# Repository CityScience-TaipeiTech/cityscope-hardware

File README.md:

# CityScope-hardware

## Environment Setup
config path
| Name|Path|
---|---
|CITYSCOPE_LIB|`YOUR_FOLDER_PATH`/cityscope-hardware/libraries
### Config Symbol Library
Preferences -> Manage Symbol Libraries

| Nickname|Library Path|
---|---
|CityScope_Component|${CITYSCOPE_LIB}/CityScope_Component.kicad_sym|

### Config Footprint Library
Preferences -> Manage Footprint Libraries
| Nickname|Library Path|
---|---
|CityScope_Component|${CITYSCOPE_LIB}/CityScope_Component.pretty|
## Generate GERBER Files for Fabrication
### Gerber Plot
In ***File*** -> ***Plot...***

### Drill Plot
In ***File*** -> ***Plot...***

## Generate .pos Files for SMT
- Make sure you set origin point for you .pos file. In the fish head PCB, set FID2 fiducial as origin. Click the icon bellow in tool set to place your origin.

- Files -> Fabrication Outputs -> Component Placement (.pos)

- The following files will be generated.

    1. PROJECT-bottom-pos.csv
    2. PROJECT-top-pos.csv

- Convert the generated file to smt machine format by a python file in `tools/` folder. 
    ``` bash
    python3 convert_form.py --file-name ../YOUR_FOLDER_PATH/PROJECT-top-pos.csv
    ```
- An output.csv will be generated in `tools/`. 
- If the footprint name is too long, for example "JST_SH_BM03B-SRSS-TB_1x03-1MP_P1.00mm_Vertical
", please make it shorter or just delete this row.

## Generating BOM Sheet
### Requirements
- Install BOM extension:`Interactive Html Bom` in the Plugin And Content Manager.

### Generate BOM
- Open your `PCB Editor` -> ***Tools*** -> ***External Plugins*** -> ***Generate Interactive Html Bom***

## Release Files Structure
1. GERBERs/
2. bom/
3. PROJECT_v1_0.pdf
4. PROJECT_3d_v1_0.png
5. PROJECT_3d_v1_0.step
6. PROJECT_gerber_v1_0.zip

# Recommend Plugins
1. Interactive Html Bom
2. pcb-action-tools
3. KiKit
4. KiBuzzard

## KiKit Panelize
### Fisheye configuration
``` json
{
    "layout": {
        "hspace": "3.2mm",
        "vspace": "3.2mm",
        "rotation": "45deg",
        "rows": "6",
        "cols": "5"
    },
    "tabs": {
        "vwidth": "3.2mm",
        "hwidth": "3.2mm"
    },
    "cuts": {
        "type": "mousebites"
    },
    "framing": {
        "type": "frame",
        "hspace": "3.2mm",
        "vspace": "3.2mm",
        "width": "3.2mm"
    }
}
```

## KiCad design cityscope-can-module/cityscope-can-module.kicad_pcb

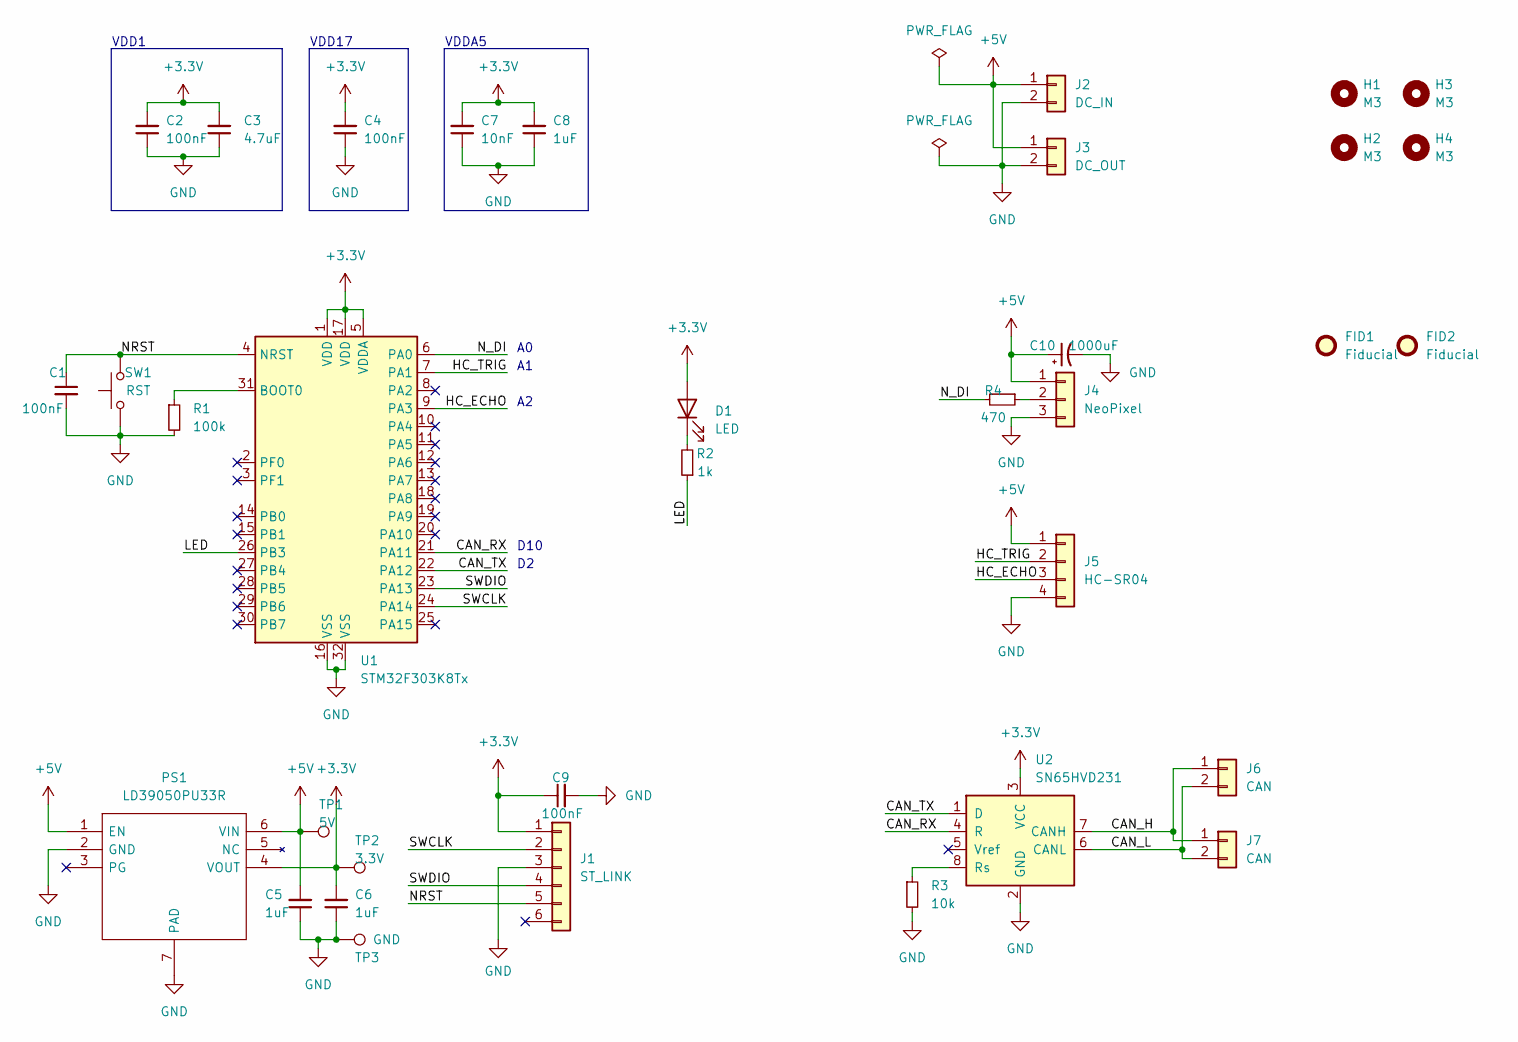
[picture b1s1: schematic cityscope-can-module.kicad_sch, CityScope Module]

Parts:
C1, C2, C4: 100nF; C_0603_1608Metric
C3: 4.7uF; C_0603_1608Metric
C5, C6, C8: 1uF; C_0603_1608Metric
C7: 10nF; C_0603_1608Metric
C9: 100nF; C_0603_1608Metric; Manufacturer_Part_Number CC603KRX7R8BB104; Mouser Part Number 603-CC603KRX7R8BB104
C10: 1000uF; CP_Radial_D8.0mm_P3.50mm
D1: LED; LED_0603_1608Metric
FID1, FID2: Fiducial; Fiducial_0.75mm_Mask1.5mm
H1, H2, H3, H4: M3; MountingHole_3.2mm_M3
J1: ST_LINK; JST_SH_BM06B-SRSS-TB_1x06-1MP_P1.00mm_Vertical; Mouser Part Number local store
J2: DC_IN; AMASS_XT30PW-M_1x02_P2.50mm_Horizontal
J3: DC_OUT; AMASS_XT30PW-F_1x02_P2.50mm_Horizontal
J4: NeoPixel; JST_PH_S3B-PH-SM4-TB_1x03-1MP_P2.00mm_Horizontal
J5: HC-SR04; JST_PH_S4B-PH-SM4-TB_1x04-1MP_P2.00mm_Horizontal
J6, J7: CAN; JST_PH_S2B-PH-SM4-TB_1x02-1MP_P2.00mm_Horizontal
PS1: LD39050PU33R; SON95P300X300X100-7N-D; Manufacturer_Part_Number LD39050PU33R; Mouser Part Number 511-LD39050PU33R
R1: 100k; R_0603_1608Metric
R2: 1k; R_0603_1608Metric
R3: 10k; R_0603_1608Metric
R4: 470; R_0603_1608Metric
SW1: RST; SW_SPST_TL3305A
TP1: 5V; TestPoint_Pad_D1.0mm
TP2: 3.3V; TestPoint_Pad_D1.0mm
TP3: GND; TestPoint_Pad_D1.0mm
U1: STM32F303K8Tx; LQFP-32_7x7mm_P0.8mm
U2: SN65HVD231; SOIC-8_3.9x4.9mm_P1.27mm

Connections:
+3.3V: C2.2, C3.2, C4.2, C6.2, C7.2, C8.2, C9.1, D1.2 (A), J1.1, PS1.4 (VOUT), TP2.1, U1.1 (VDD), U1.5 (VDDA), U1.17 (VDD), U2.3 (VCC)
+5V: C5.2, C10.1, J2.1, J3.1, J4.1, J5.1, PS1.1 (EN), PS1.6 (VIN), TP1.1
/CAN_H: J6.1, J7.1, U2.7 (CANH)
/CAN_L: J6.2, J7.2, U2.6 (CANL)
/CAN_RX: U1.21 (PA11), U2.4 (R)
/CAN_TX: U1.22 (PA12), U2.1 (D)
/HC_ECHO: J5.3, U1.9 (PA3)
/HC_TRIG: J5.2, U1.7 (PA1)
/LED: R2.1, U1.26 (PB3)
/NRST: C1.1, J1.5, SW1.2, U1.4 (NRST)
/N_DI: R4.2, U1.6 (PA0)
/SWCLK: J1.2, U1.24 (PA14)
/SWDIO: J1.4, U1.23 (PA13)
GND: C1.2, C2.1, C3.1, C4.1, C5.1, C6.1, C7.1, C8.1, C9.2, C10.2, J1.3, J2.2, J3.2, J4.3, J5.4, PS1.2 (GND), PS1.7 (PAD), R1.2, R3.2, SW1.1, TP3.1, U1.16 (VSS), U1.32 (VSS), U2.2 (GND)
unnamed: D1.1 (K), R2.2
unnamed: J4.2, R4.1
unnamed: R1.1, U1.31 (BOOT0)
unnamed: R3.1, U2.8 (Rs)

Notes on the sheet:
VDD1
D10
VDDA5
VDD17

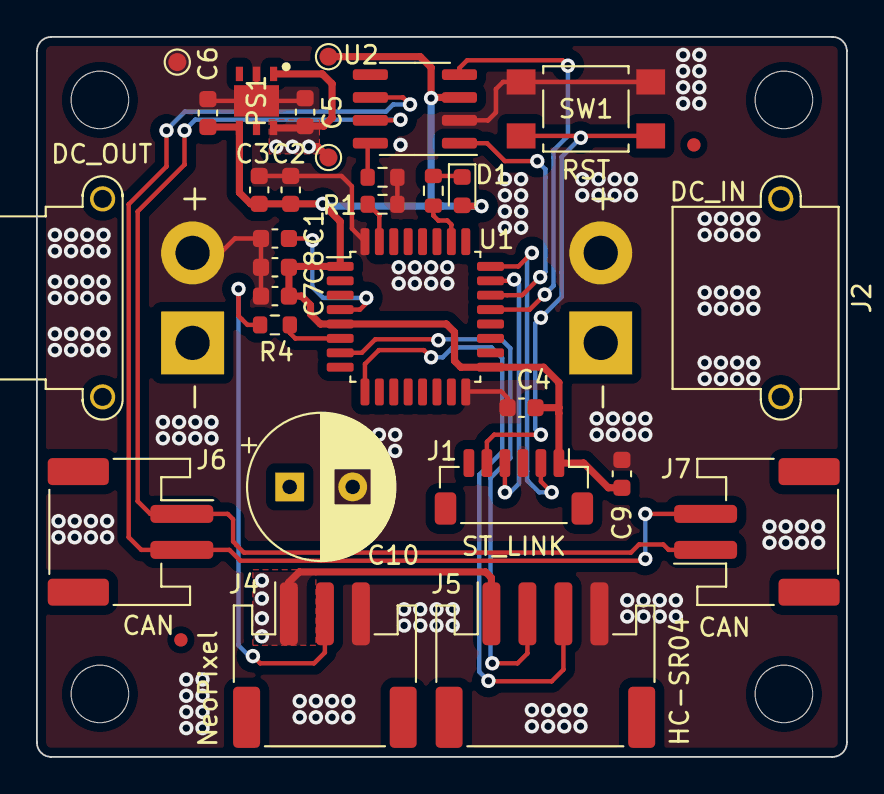
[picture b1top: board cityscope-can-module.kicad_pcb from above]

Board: 4 copper layers, 45.0 x 40.0 mm, 35 parts (0 on the bottom side), 18 nets.

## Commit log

2023-02-22 add doc
2023-02-22 release cityscope can moudule v1.0
2023-02-22 re-arrang file structure
2023-02-22 add gitignore
2023-02-22 remove .vscode
2023-02-22 add release note
2023-03-02 add 3D module
2023-03-02 add tools for convert .pos file to SMT machine
2023-03-02 add file for SMT machine
